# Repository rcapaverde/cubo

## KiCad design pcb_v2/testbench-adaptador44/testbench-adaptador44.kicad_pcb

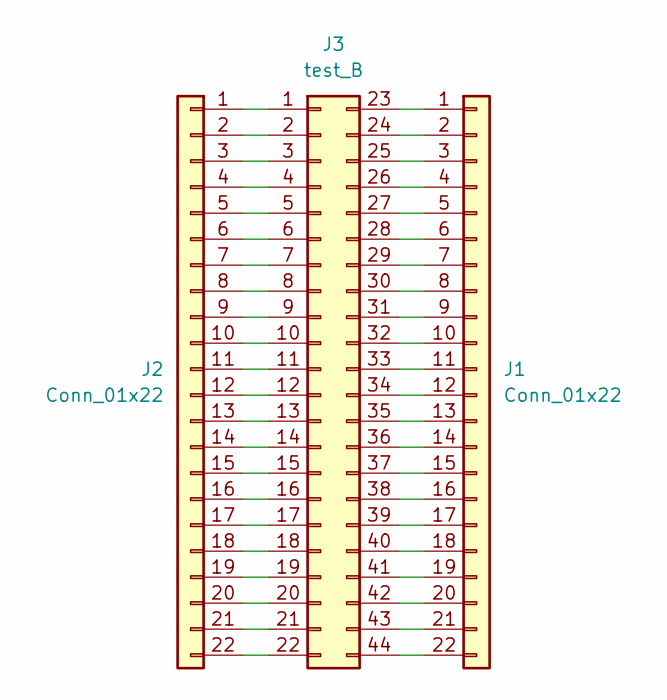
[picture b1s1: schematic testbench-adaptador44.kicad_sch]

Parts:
J1, J2: Conn_01x22; PinHeader_1x22_P2.54mm_Vertical
J3: test_B; male-edge-connector-44

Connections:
unnamed: J1.1, J3.23
unnamed: J1.2, J3.24
unnamed: J1.3, J3.25
unnamed: J1.4, J3.26
unnamed: J1.5, J3.27
unnamed: J1.6, J3.28
unnamed: J1.7, J3.29
unnamed: J1.8, J3.30
unnamed: J1.9, J3.31
unnamed: J1.10, J3.32
unnamed: J1.11, J3.33
unnamed: J1.12, J3.34
unnamed: J1.13, J3.35
unnamed: J1.14, J3.36
unnamed: J1.15, J3.37
unnamed: J1.16, J3.38
unnamed: J1.17, J3.39
unnamed: J1.18, J3.40
unnamed: J1.19, J3.41
unnamed: J1.20, J3.42
unnamed: J1.21, J3.43
unnamed: J1.22, J3.44
unnamed: J2.1, J3.1
unnamed: J2.2, J3.2
unnamed: J2.3, J3.3
unnamed: J2.4, J3.4
unnamed: J2.5, J3.5
unnamed: J2.6, J3.6
unnamed: J2.7, J3.7
unnamed: J2.8, J3.8
unnamed: J2.9, J3.9
unnamed: J2.10, J3.10
unnamed: J2.11, J3.11
unnamed: J2.12, J3.12
unnamed: J2.13, J3.13
unnamed: J2.14, J3.14
unnamed: J2.15, J3.15
unnamed: J2.16, J3.16
unnamed: J2.17, J3.17
unnamed: J2.18, J3.18
unnamed: J2.19, J3.19
unnamed: J2.20, J3.20
unnamed: J2.21, J3.21
unnamed: J2.22, J3.22

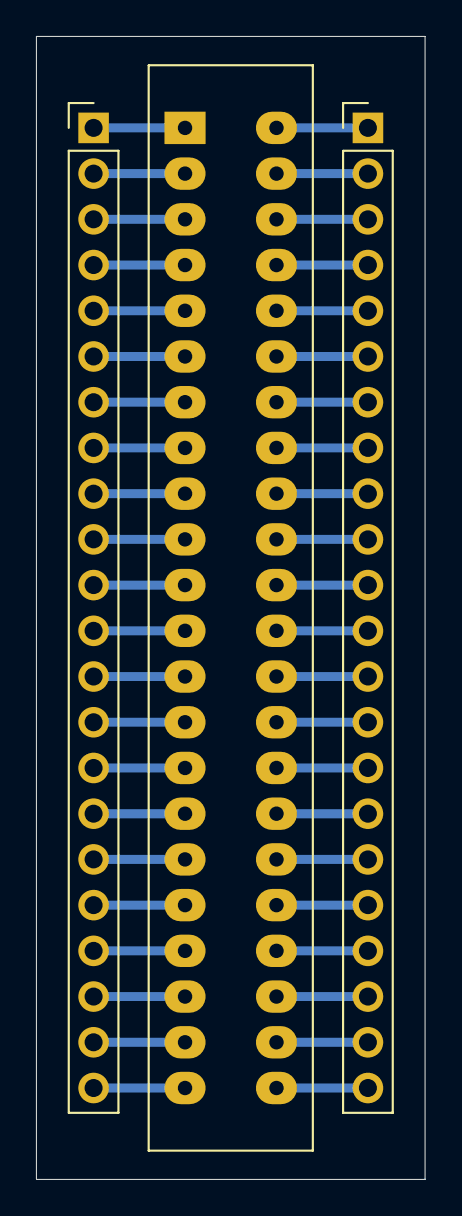
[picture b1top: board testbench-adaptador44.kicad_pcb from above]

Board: 2 copper layers, 21.6 x 63.5 mm, 3 parts (0 on the bottom side), 44 nets.

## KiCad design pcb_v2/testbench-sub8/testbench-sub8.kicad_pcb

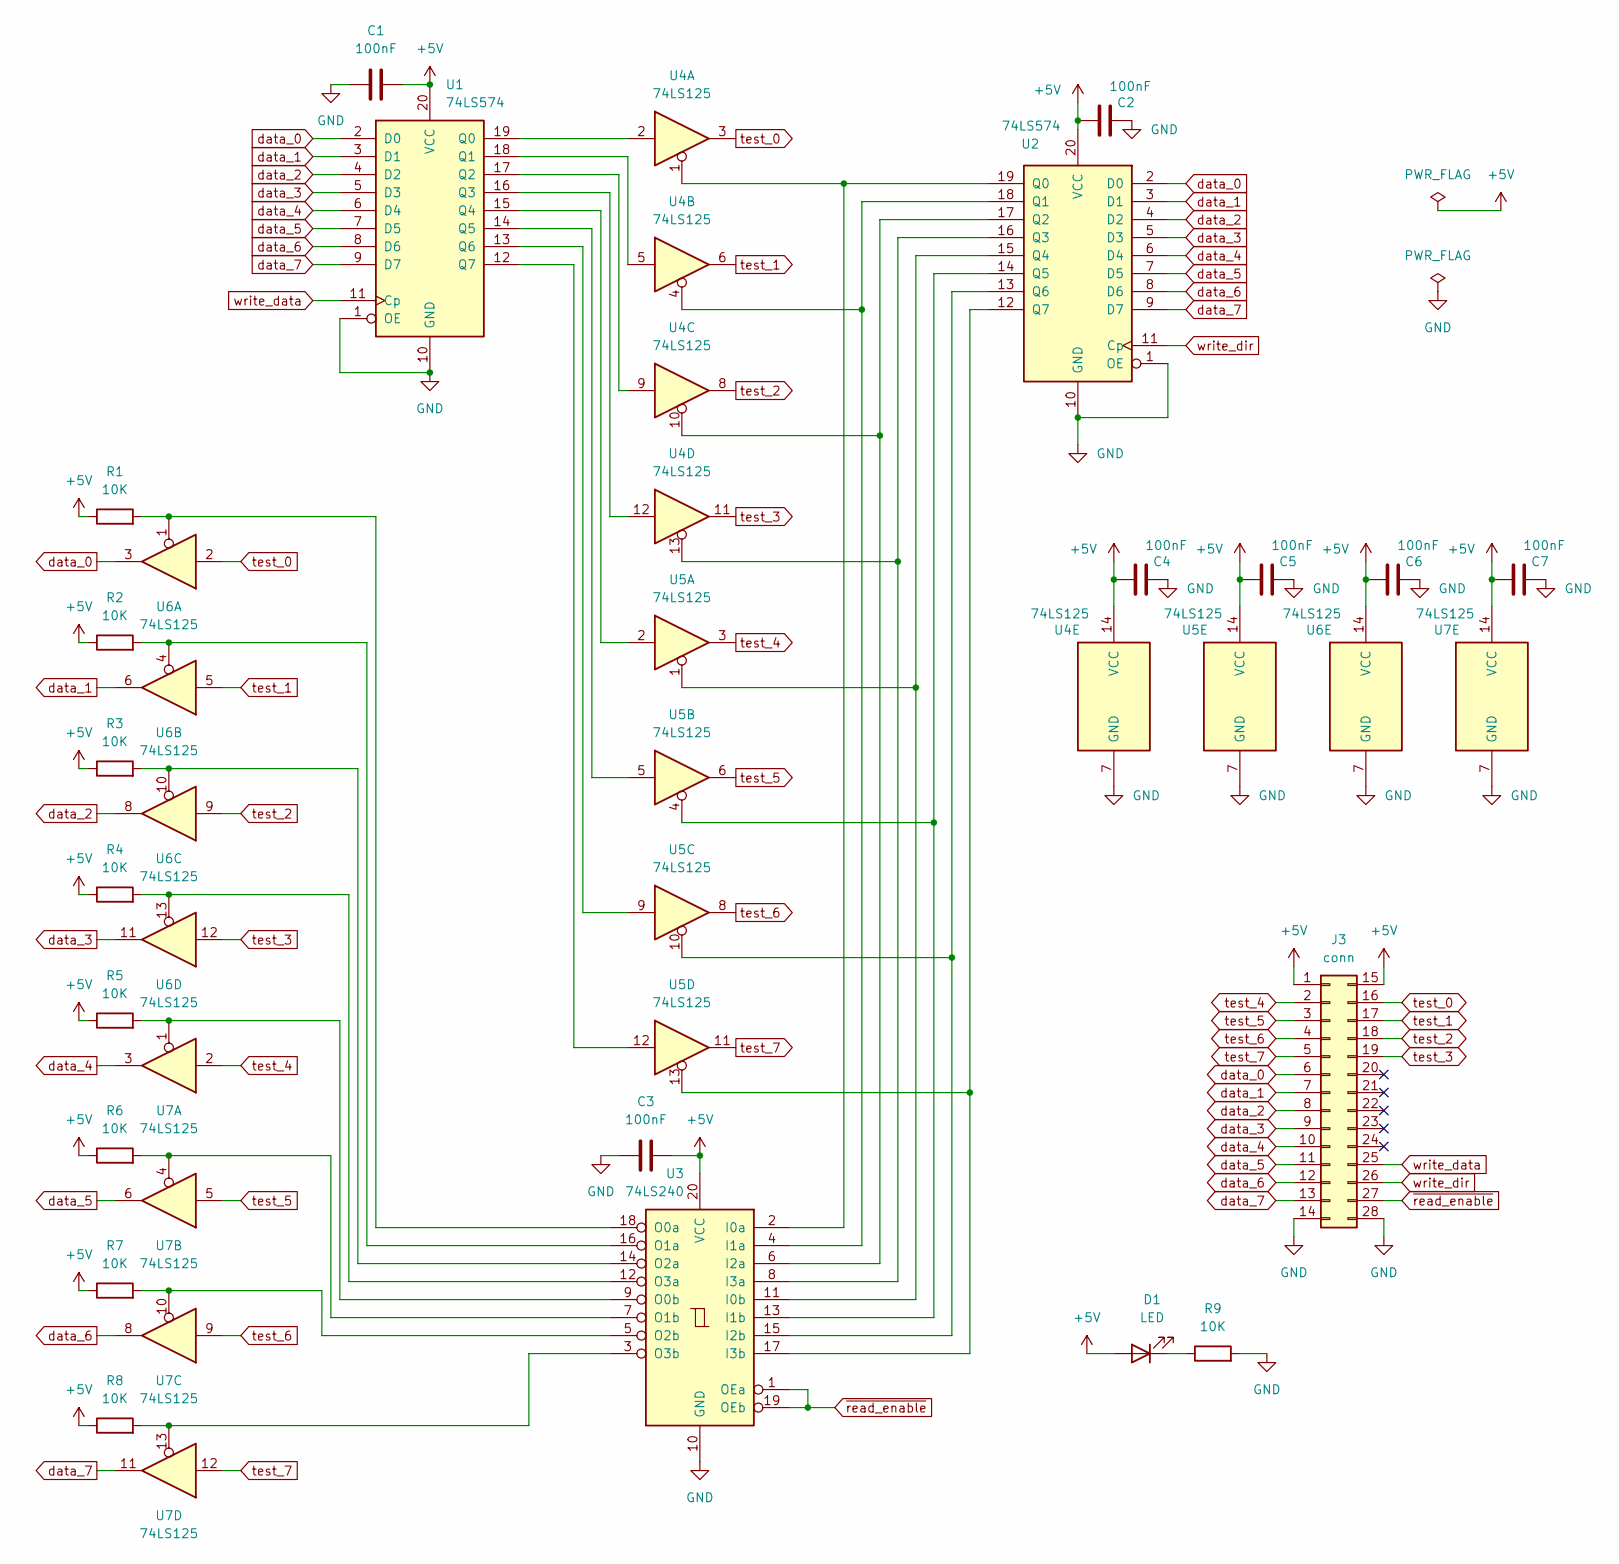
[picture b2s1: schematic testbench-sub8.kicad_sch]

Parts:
C1, C2, C3, C4, C5, C6, C7: 100nF; C_Disc_D4.7mm_W2.5mm_P5.00mm
D1: LED; LED_D5.0mm
J3: conn; edge-conector-14
R1, R2, R3, R4, R5, R6, R7, R8, R9: 10K; R_Axial_DIN0204_L3.6mm_D1.6mm_P7.62mm_Horizontal
U1, U2: 74LS574; DIP-20_W7.62mm
U3: 74LS240; DIP-20_W7.62mm
U4, U5, U6, U7: 74LS125; DIP-14_W7.62mm

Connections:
+5V: C1.2, C2.2, C3.2, C4.2, C5.2, C6.2, C7.2, D1.2 (A), J3.1, J3.15, R1.1, R2.1, R3.1, R4.1, R5.1, R6.1, R7.1, R8.1, U1.20 (VCC), U2.20 (VCC), U3.20 (VCC), U4.14 (VCC), U5.14 (VCC), U6.14 (VCC), U7.14 (VCC)
GND: C1.1, C2.1, C3.1, C4.1, C5.1, C6.1, C7.1, J3.14, J3.28, R9.2, U1.1 (OE), U1.10 (GND), U2.1 (OE), U2.10 (GND), U3.10 (GND), U4.7 (GND), U5.7 (GND), U6.7 (GND), U7.7 (GND)
unnamed: D1.1 (K), R9.1
unnamed: U1.19 (Q0), U4.2
unnamed: U1.18 (Q1), U4.5
unnamed: U1.17 (Q2), U4.9
unnamed: U1.16 (Q3), U4.12
unnamed: U1.15 (Q4), U5.2
unnamed: U1.14 (Q5), U5.5
unnamed: U1.13 (Q6), U5.9
unnamed: U1.12 (Q7), U5.12
unnamed: U2.19 (Q0), U3.2 (I0a), U4.1
unnamed: U2.18 (Q1), U3.4 (I1a), U4.4
unnamed: U2.17 (Q2), U3.6 (I2a), U4.10
unnamed: U2.16 (Q3), U3.8 (I3a), U4.13
unnamed: U2.15 (Q4), U3.11 (I0b), U5.1
unnamed: U2.14 (Q5), U3.13 (I1b), U5.4
unnamed: U2.13 (Q6), U3.15 (I2b), U5.10
unnamed: U2.12 (Q7), U3.17 (I3b), U5.13
unnamed: R1.2, U3.18 (O0a), U6.1
unnamed: R5.2, U3.9 (O0b), U7.1
unnamed: R2.2, U3.16 (O1a), U6.4
unnamed: R6.2, U3.7 (O1b), U7.4
unnamed: R3.2, U3.14 (O2a), U6.10
unnamed: R7.2, U3.5 (O2b), U7.10
unnamed: R4.2, U3.12 (O3a), U6.13
unnamed: R8.2, U3.3 (O3b), U7.13
data_0: J3.6, U1.2 (D0), U2.2 (D0), U6.3
data_1: J3.7, U1.3 (D1), U2.3 (D1), U6.6
data_2: J3.8, U1.4 (D2), U2.4 (D2), U6.8
data_3: J3.9, U1.5 (D3), U2.5 (D3), U6.11
data_4: J3.10, U1.6 (D4), U2.6 (D4), U7.3
data_5: J3.11, U1.7 (D5), U2.7 (D5), U7.6
data_6: J3.12, U1.8 (D6), U2.8 (D6), U7.8
data_7: J3.13, U1.9 (D7), U2.9 (D7), U7.11
test_0: J3.16, U4.3, U6.2
test_1: J3.17, U4.6, U6.5
test_2: J3.18, U4.8, U6.9
test_3: J3.19, U4.11, U6.12
test_4: J3.2, U5.3, U7.2
test_5: J3.3, U5.6, U7.5
test_6: J3.4, U5.8, U7.9
test_7: J3.5, U5.11, U7.12
write_data: J3.25, U1.11 (Cp)
write_dir: J3.26, U2.11 (Cp)
~read_enable: J3.27, U3.1 (OEa), U3.19 (OEb)

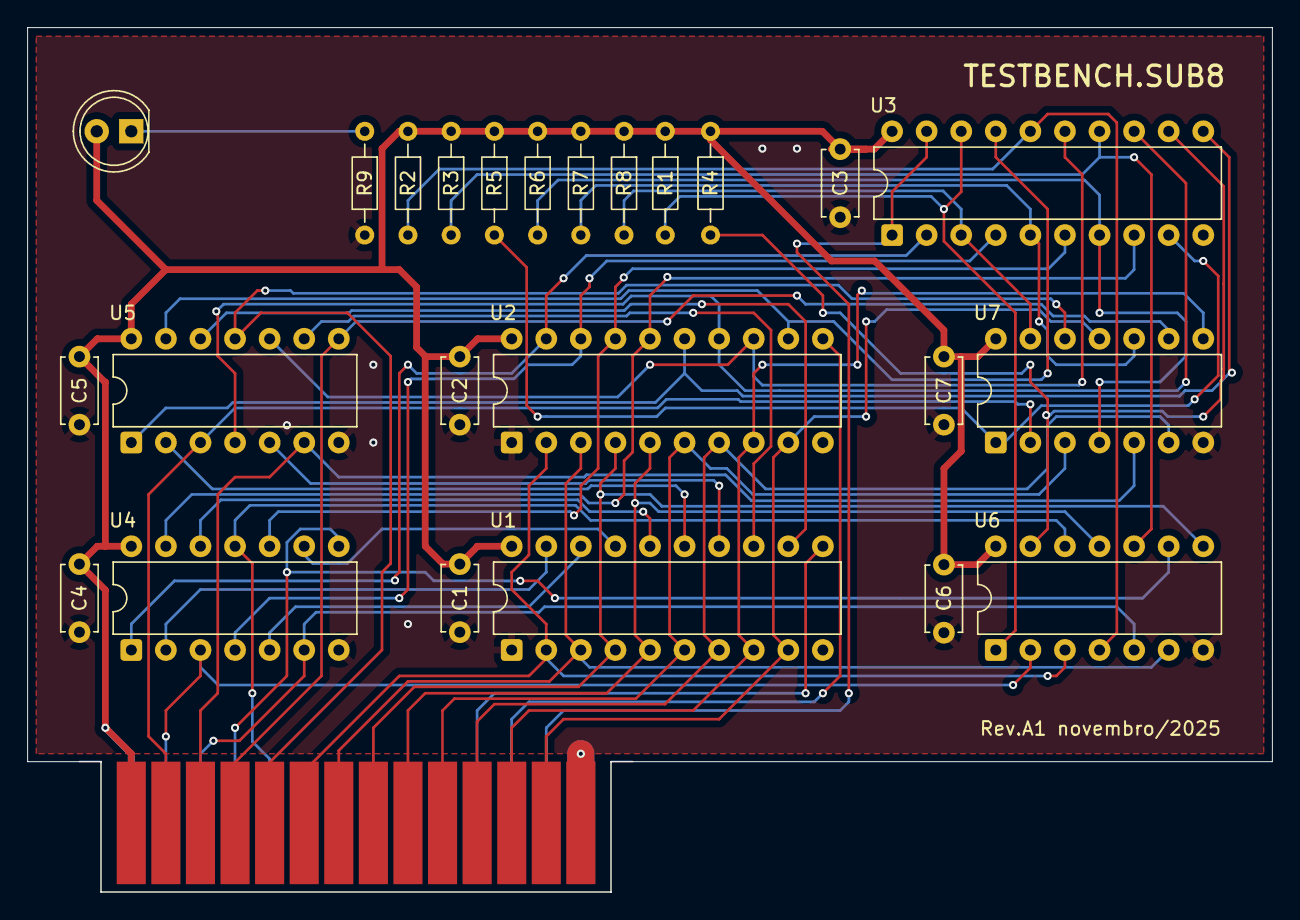
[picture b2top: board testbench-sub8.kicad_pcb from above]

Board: 2 copper layers, 91.4 x 63.5 mm, 25 parts (0 on the bottom side), 46 nets.

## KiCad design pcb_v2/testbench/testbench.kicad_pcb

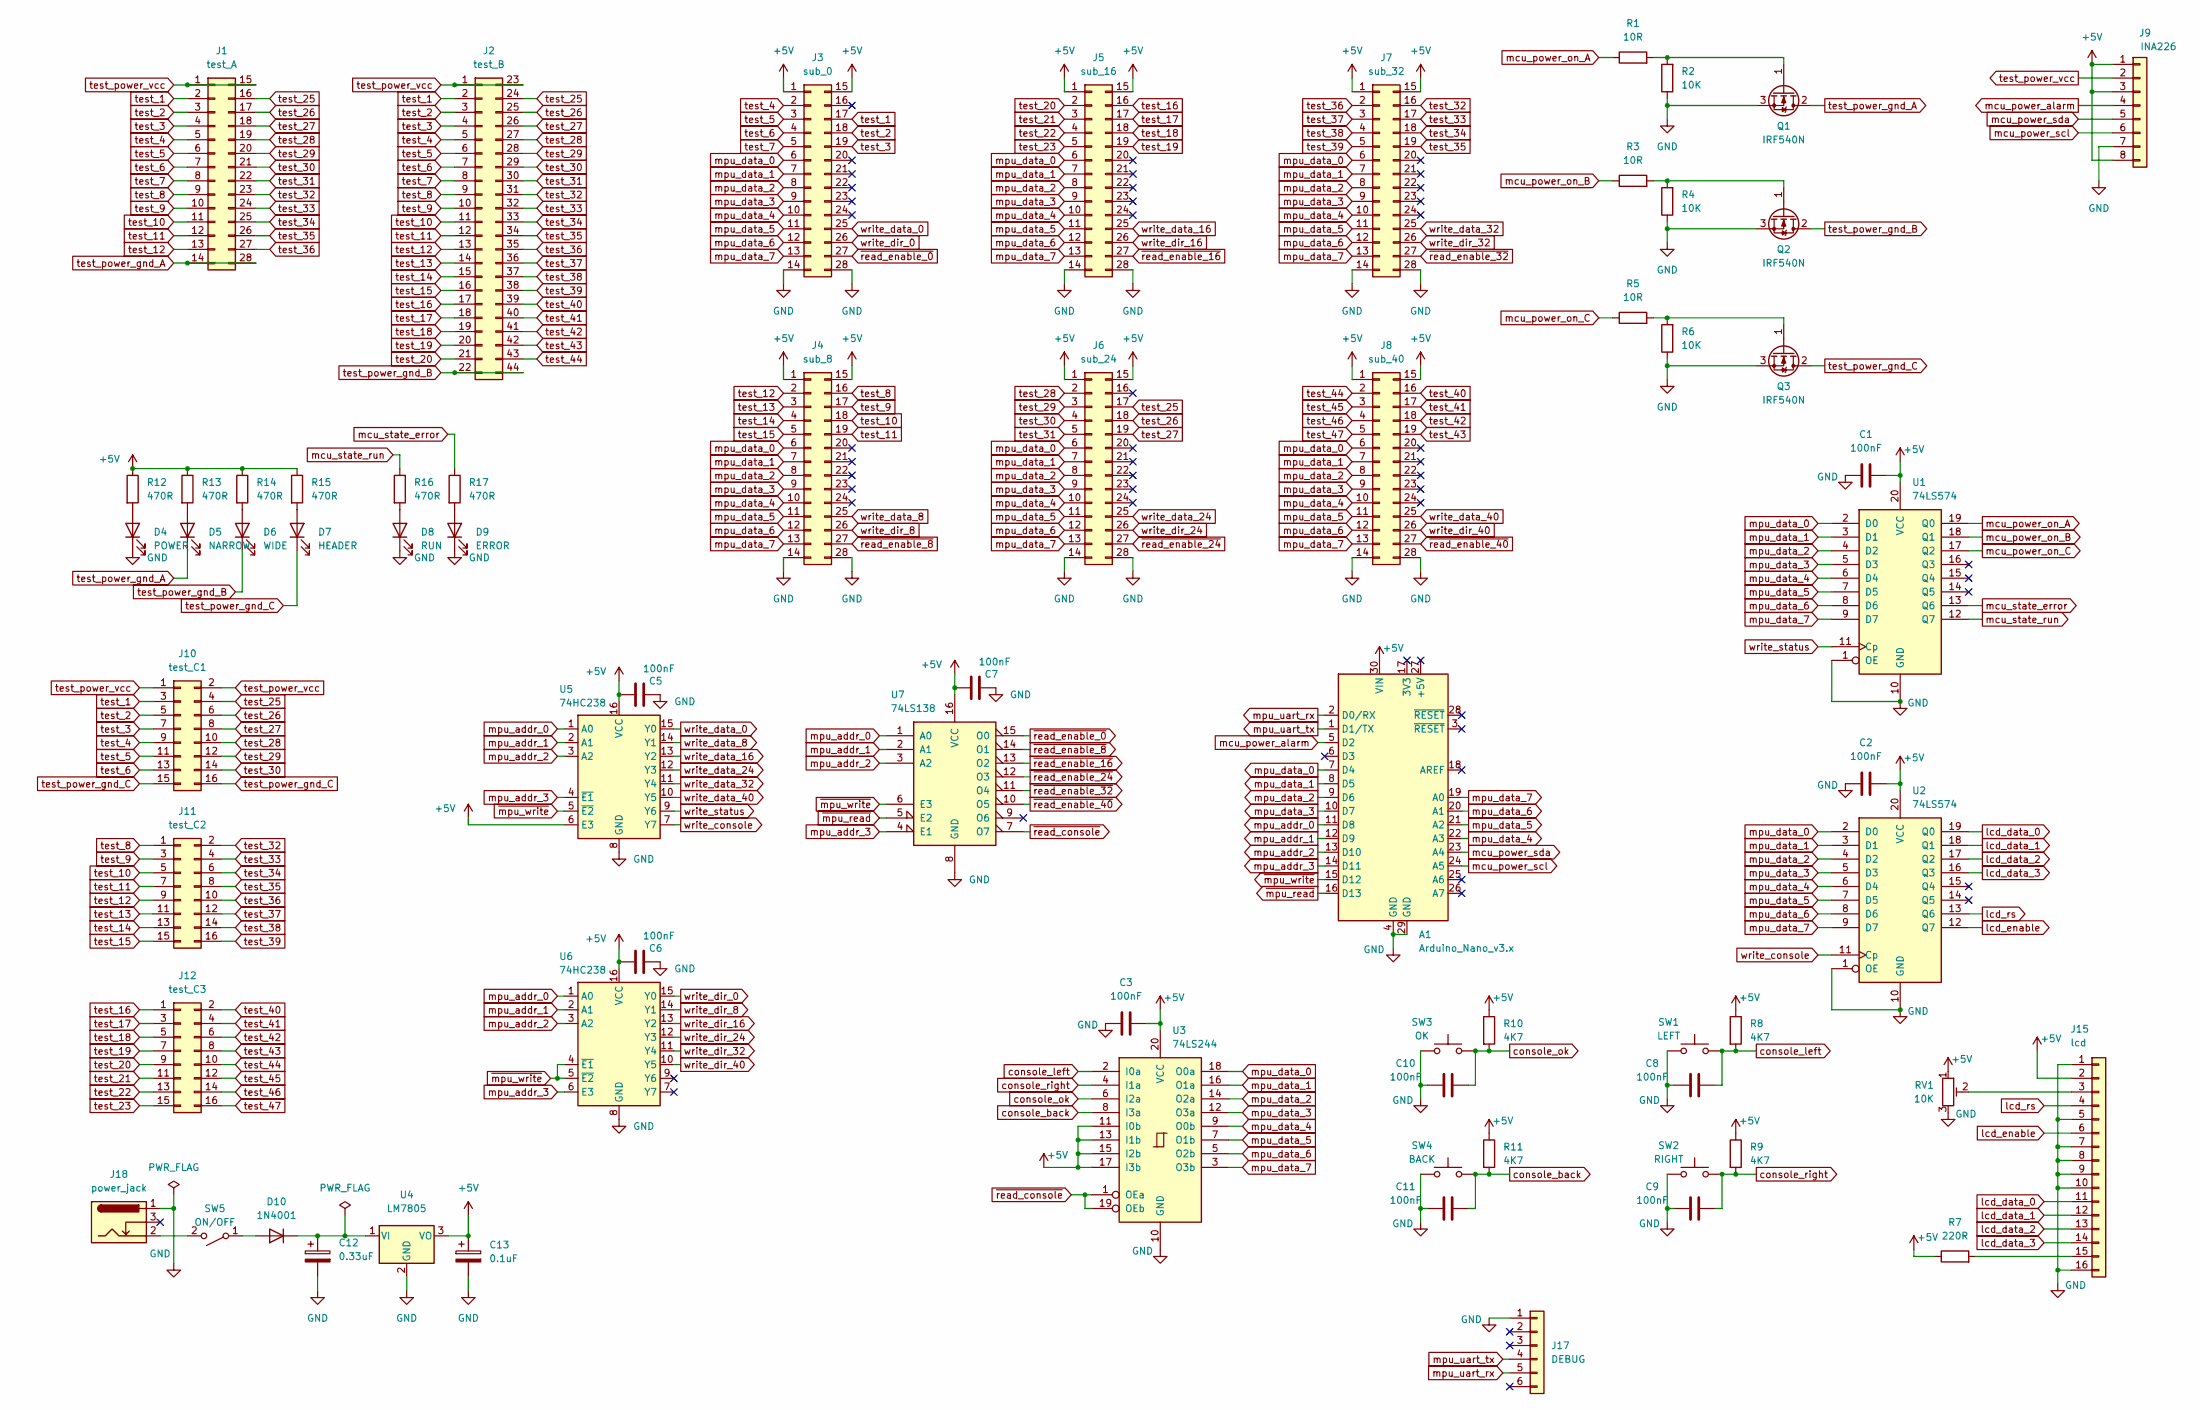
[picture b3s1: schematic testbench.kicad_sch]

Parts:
A1: Arduino_Nano_v3.x; Arduino_Nano
C1, C2, C3, C5, C6, C7, C8, C9, C10, C11: 100nF; C_Disc_D4.7mm_W2.5mm_P5.00mm
C12: 0.33uF; CP_Radial_D5.0mm_P2.50mm
C13: 0.1uF; CP_Radial_D5.0mm_P2.50mm
D4: POWER; LED_D5.0mm
D5: NARROW; LED_D5.0mm
D6: WIDE; LED_D5.0mm
D7: HEADER; LED_D5.0mm
D8: RUN; LED_D5.0mm
D9: ERROR; LED_D5.0mm
D10: 1N4001; D_DO-41_SOD81_P10.16mm_Horizontal
J1: test_A; male-edge-connector-28
J2: test_B; male-edge-connector-44
J3: sub_0; male-edge-connector-28
J4: sub_8; male-edge-connector-28
J5: sub_16; male-edge-connector-28
J6: sub_24; male-edge-connector-28
J7: sub_32; male-edge-connector-28
J8: sub_40; male-edge-connector-28
J9: INA226; PinSocket_1x08_P2.54mm_Vertical
J10: test_C1; PinHeader_2x08_P2.54mm_Vertical
J11: test_C2; PinHeader_2x08_P2.54mm_Vertical
J12: test_C3; PinHeader_2x08_P2.54mm_Vertical
J15: lcd; PinSocket_1x16_P2.54mm_Vertical
J17: DEBUG; PinSocket_1x06_P2.54mm_Vertical
J18: power_jack; BarrelJack_Horizontal
Q1, Q2, Q3: IRF540N; TO-220-3_Vertical
R1, R3, R5: 10R; R_Axial_DIN0207_L6.3mm_D2.5mm_P7.62mm_Horizontal
R2, R4, R6: 10K; R_Axial_DIN0207_L6.3mm_D2.5mm_P7.62mm_Horizontal
R7: 220R; R_Axial_DIN0207_L6.3mm_D2.5mm_P7.62mm_Horizontal
R8, R9, R10, R11: 4K7; R_Axial_DIN0207_L6.3mm_D2.5mm_P7.62mm_Horizontal
R12, R13, R14, R15, R16, R17: 470R; R_Axial_DIN0207_L6.3mm_D2.5mm_P7.62mm_Horizontal
RV1: 10K; Potentiometer_ACP_CA9-H5_Horizontal
SW1: LEFT; SW_PUSH_6mm
SW2: RIGHT; SW_PUSH_6mm
SW3: OK; SW_PUSH_6mm
SW4: BACK; SW_PUSH_6mm
SW5: ON/OFF; jrx
U1, U2: 74LS574; DIP-20_W7.62mm
U3: 74LS244; DIP-20_W7.62mm
U4: LM7805; TO-220-3_Vertical
U5, U6: 74HC238; DIP-16_W7.62mm
U7: 74LS138; DIP-16_W7.62mm

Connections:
+5V: A1.30 (VIN), C1.2, C2.2, C3.2, C5.2, C6.2, C7.2, C13.1, J3.1, J3.15, J4.1, J4.15, J5.1, J5.15, J6.1, J6.15, J7.1, J7.15, J8.1, J8.15, J9.1, J9.3, J9.8, J15.2, R7.1, R8.1, R9.1, R10.1, R11.1, R12.1, R13.1, R14.1, R15.1, RV1.1, U1.20 (VCC), U2.20 (VCC), U3.11 (I0b), U3.13 (I1b), U3.15 (I2b), U3.17 (I3b), U3.20 (VCC), U4.3 (VO), U5.6 (E3), U5.16 (VCC), U6.16 (VCC), U7.16 (VCC)
GND: A1.4 (GND), A1.29 (GND), C1.1, C2.1, C3.1, C5.1, C6.1, C7.1, C8.1, C9.1, C10.1, C11.1, C12.2, C13.2, D4.1 (K), D8.1 (K), D9.1 (K), J3.14, J3.28, J4.14, J4.28, J5.14, J5.28, J6.14, J6.28, J7.14, J7.28, J8.14, J8.28, J9.7, J15.1, J15.5, J15.7, J15.8, J15.9, J15.10, J15.16, J17.1, J18.1, Q1.3 (S), Q2.3 (S), Q3.3 (S), R2.1, R4.1, R6.1, RV1.3, SW1.1, SW2.1, SW3.1, SW4.1, U1.1 (OE), U1.10 (GND), U2.1 (OE), U2.10 (GND), U3.10 (GND), U4.2 (GND), U5.8 (GND), U6.8 (GND), U7.8 (GND)
unnamed: D4.2 (A), R12.2
unnamed: D5.2 (A), R13.2
unnamed: D6.2 (A), R14.2
unnamed: D7.2 (A), R15.2
unnamed: D8.2 (A), R16.2
unnamed: D9.2 (A), R17.2
unnamed: D10.2 (A), SW5.1 (A)
unnamed: C12.1, D10.1 (K), U4.1 (VI)
unnamed: J15.3, RV1.2
unnamed: J15.15, R7.2
unnamed: Q1.1 (G), R1.2, R2.2
unnamed: Q2.1 (G), R3.2, R4.2
unnamed: Q3.1 (G), R5.2, R6.2
unnamed: J18.2, SW5.2 (B)
console_back: C11.2, R11.2, SW4.2, U3.8 (I3a)
console_left: C8.2, R8.2, SW1.2, U3.2 (I0a)
console_ok: C10.2, R10.2, SW3.2, U3.6 (I2a)
console_right: C9.2, R9.2, SW2.2, U3.4 (I1a)
lcd_data_0: J15.11, U2.19 (Q0)
lcd_data_1: J15.12, U2.18 (Q1)
lcd_data_2: J15.13, U2.17 (Q2)
lcd_data_3: J15.14, U2.16 (Q3)
lcd_enable: J15.6, U2.12 (Q7)
lcd_rs: J15.4, U2.13 (Q6)
mcu_power_alarm: A1.5 (D2), J9.4
mcu_power_on_A: R1.1, U1.19 (Q0)
mcu_power_on_B: R3.1, U1.18 (Q1)
mcu_power_on_C: R5.1, U1.17 (Q2)
mcu_power_scl: A1.24 (A5), J9.6
mcu_power_sda: A1.23 (A4), J9.5
mcu_state_error: R17.1, U1.13 (Q6)
mcu_state_run: R16.1, U1.12 (Q7)
mpu_addr_0: A1.11 (D8), U5.1 (A0), U6.1 (A0), U7.1 (A0)
mpu_addr_1: A1.12 (D9), U5.2 (A1), U6.2 (A1), U7.2 (A1)
mpu_addr_2: A1.13 (D10), U5.3 (A2), U6.3 (A2), U7.3 (A2)
mpu_addr_3: A1.14 (D11), U5.4 (~E1), U6.6 (E3), U7.4 (E1)
mpu_data_0: A1.7 (D4), J3.6, J4.6, J5.6, J6.6, J7.6, J8.6, U1.2 (D0), U2.2 (D0), U3.18 (O0a)
mpu_data_1: A1.8 (D5), J3.7, J4.7, J5.7, J6.7, J7.7, J8.7, U1.3 (D1), U2.3 (D1), U3.16 (O1a)
mpu_data_2: A1.9 (D6), J3.8, J4.8, J5.8, J6.8, J7.8, J8.8, U1.4 (D2), U2.4 (D2), U3.14 (O2a)
mpu_data_3: A1.10 (D7), J3.9, J4.9, J5.9, J6.9, J7.9, J8.9, U1.5 (D3), U2.5 (D3), U3.12 (O3a)
mpu_data_4: A1.22 (A3), J3.10, J4.10, J5.10, J6.10, J7.10, J8.10, U1.6 (D4), U2.6 (D4), U3.9 (O0b)
mpu_data_5: A1.21 (A2), J3.11, J4.11, J5.11, J6.11, J7.11, J8.11, U1.7 (D5), U2.7 (D5), U3.7 (O1b)
mpu_data_6: A1.20 (A1), J3.12, J4.12, J5.12, J6.12, J7.12, J8.12, U1.8 (D6), U2.8 (D6), U3.5 (O2b)
mpu_data_7: A1.19 (A0), J3.13, J4.13, J5.13, J6.13, J7.13, J8.13, U1.9 (D7), U2.9 (D7), U3.3 (O3b)
mpu_uart_rx: A1.2 (D0/RX), J17.5
mpu_uart_tx: A1.1 (D1/TX), J17.4
test_1: J1.2, J2.2, J3.17, J10.3
test_2: J1.3, J2.3, J3.18, J10.5
test_3: J1.4, J2.4, J3.19, J10.7
test_4: J1.5, J2.5, J3.2, J10.9
test_5: J1.6, J2.6, J3.3, J10.11
test_6: J1.7, J2.7, J3.4, J10.13
test_7: J1.8, J2.8, J3.5
test_8: J1.9, J2.9, J4.16, J11.1
test_9: J1.10, J2.10, J4.17, J11.3
test_10: J1.11, J2.11, J4.18, J11.5
test_11: J1.12, J2.12, J4.19, J11.7
test_12: J1.13, J2.13, J4.2, J11.9
test_13: J2.14, J4.3, J11.11
test_14: J2.15, J4.4, J11.13
test_15: J2.16, J4.5, J11.15
test_16: J2.17, J5.16, J12.1
test_17: J2.18, J5.17, J12.3
test_18: J2.19, J5.18, J12.5
test_19: J2.20, J5.19, J12.7
test_20: J2.21, J5.2, J12.9
test_21: J5.3, J12.11
test_22: J5.4, J12.13
test_23: J5.5, J12.15
test_25: J1.16, J2.24, J6.17, J10.4
test_26: J1.17, J2.25, J6.18, J10.6
test_27: J1.18, J2.26, J6.19, J10.8
test_28: J1.19, J2.27, J6.2, J10.10
test_29: J1.20, J2.28, J6.3, J10.12
test_30: J1.21, J2.29, J6.4, J10.14
test_31: J1.22, J2.30, J6.5
test_32: J1.23, J2.31, J7.16, J11.2
test_33: J1.24, J2.32, J7.17, J11.4
test_34: J1.25, J2.33, J7.18, J11.6
test_35: J1.26, J2.34, J7.19, J11.8
test_36: J1.27, J2.35, J7.2, J11.10
test_37: J2.36, J7.3, J11.12
test_38: J2.37, J7.4, J11.14
test_39: J2.38, J7.5, J11.16
test_40: J2.39, J8.16, J12.2
test_41: J2.40, J8.17, J12.4
test_42: J2.41, J8.18, J12.6
test_43: J2.42, J8.19, J12.8
test_44: J2.43, J8.2, J12.10
test_45: J8.3, J12.12
test_46: J8.4, J12.14
test_47: J8.5, J12.16
test_power_gnd_A: D5.1 (K), J1.14, J1.28, Q1.2 (D)
test_power_gnd_B: D6.1 (K), J2.22, J2.44, Q2.2 (D)
test_power_gnd_C: D7.1 (K), J10.15, J10.16, Q3.2 (D)
test_power_vcc: J1.1, J1.15, J2.1, J2.23, J9.2, J10.1, J10.2
write_console: U2.11 (Cp), U5.7 (Y7)
write_data_0: J3.25, U5.15 (Y0)
write_data_8: J4.25, U5.14 (Y1)
write_data_16: J5.25, U5.13 (Y2)
write_data_24: J6.25, U5.12 (Y3)
write_data_32: J7.25, U5.11 (Y4)
write_data_40: J8.25, U5.10 (Y5)
write_dir_0: J3.26, U6.15 (Y0)
write_dir_8: J4.26, U6.14 (Y1)
write_dir_16: J5.26, U6.13 (Y2)
write_dir_24: J6.26, U6.12 (Y3)
write_dir_32: J7.26, U6.11 (Y4)
write_dir_40: J8.26, U6.10 (Y5)
write_status: U1.11 (Cp), U5.9 (Y6)
~mpu_read: A1.16 (D13), U7.5 (E2)
~mpu_write: A1.15 (D12), U5.5 (~E2), U6.4 (~E1), U6.5 (~E2), U7.6 (E3)
~read_console: U3.1 (OEa), U3.19 (OEb), U7.7 (O7)
~read_enable_0: J3.27, U7.15 (O0)
~read_enable_8: J4.27, U7.14 (O1)
~read_enable_16: J5.27, U7.13 (O2)
~read_enable_24: J6.27, U7.12 (O3)
~read_enable_32: J7.27, U7.11 (O4)
~read_enable_40: J8.27, U7.10 (O5)

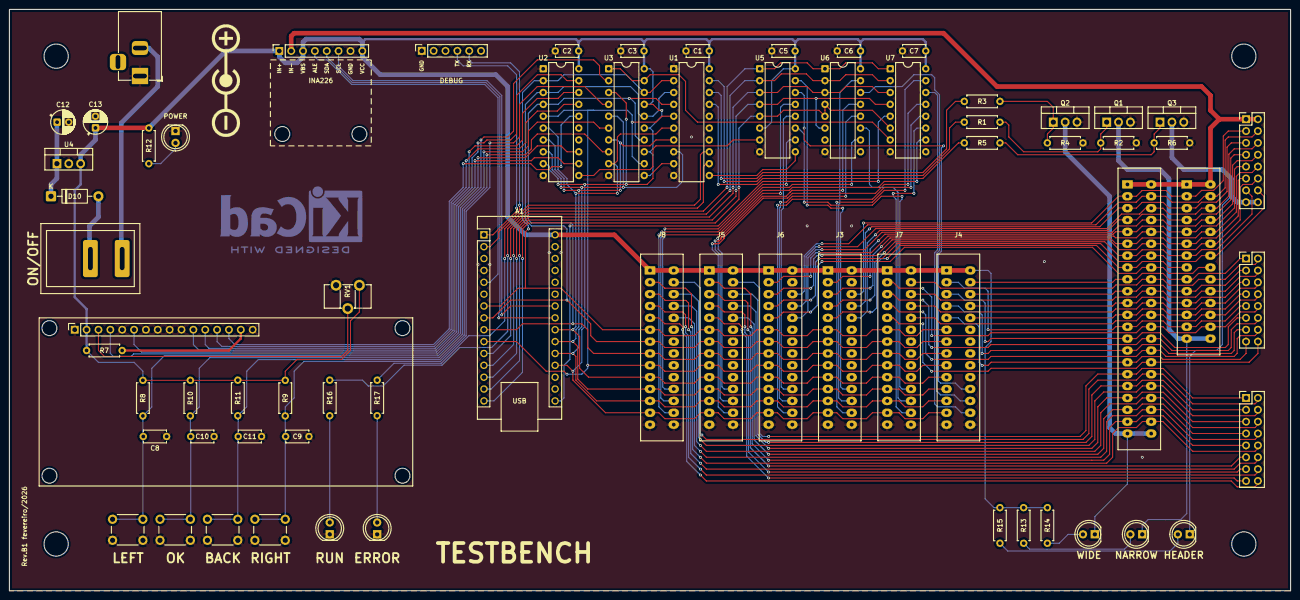
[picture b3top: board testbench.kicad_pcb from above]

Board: 2 copper layers, 274.3 x 124.5 mm, 68 parts (0 on the bottom side), 121 nets.

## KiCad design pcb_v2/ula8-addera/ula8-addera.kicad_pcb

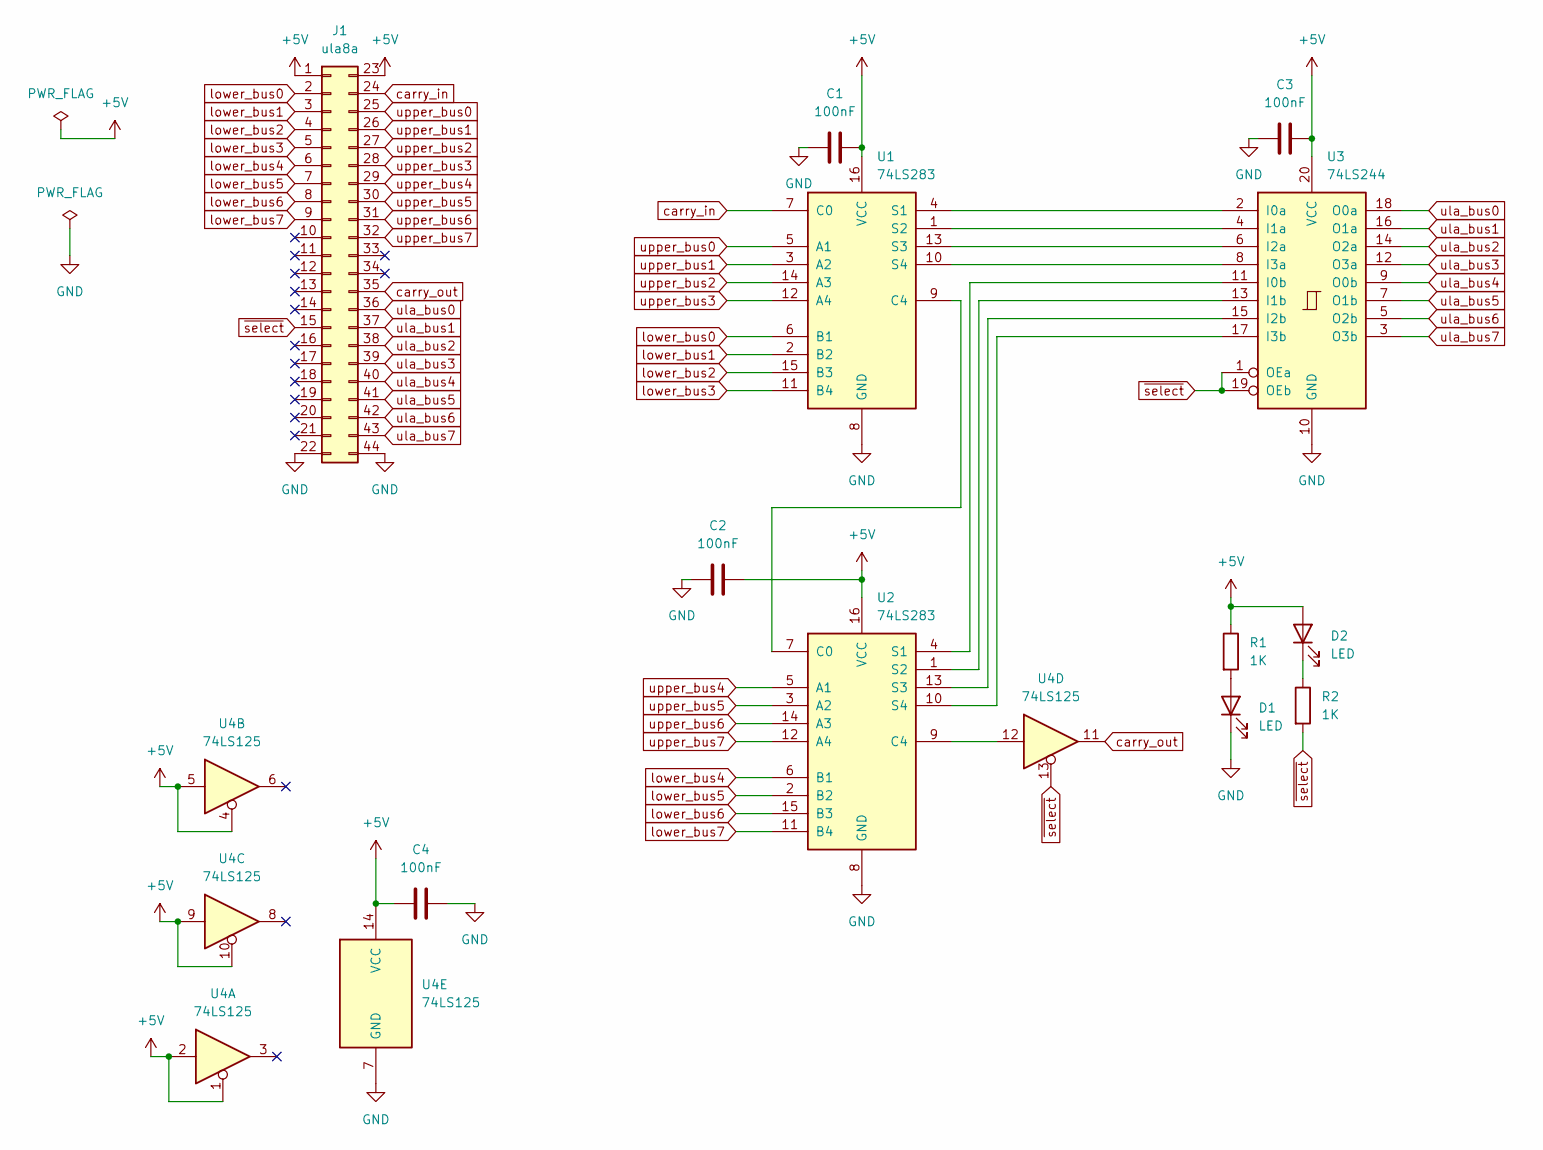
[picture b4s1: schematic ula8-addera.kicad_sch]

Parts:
C1, C2, C3, C4: 100nF; C_Disc_D5.1mm_W3.2mm_P5.00mm
D1, D2: LED; LED_D5.0mm
J1: ula8a; edge-connector-44
R1, R2: 1K; R_Axial_DIN0207_L6.3mm_D2.5mm_P7.62mm_Horizontal
U1, U2: 74LS283; DIP-16_W7.62mm
U3: 74LS244; DIP-20_W7.62mm
U4: 74LS125; DIP-14_W7.62mm

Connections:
+5V: C1.2, C2.2, C3.2, C4.1, D2.2 (A), J1.1, J1.23, R1.1, U1.16 (VCC), U2.16 (VCC), U3.20 (VCC), U4.1, U4.2, U4.4, U4.5, U4.9, U4.10, U4.14 (VCC)
GND: C1.1, C2.1, C3.1, C4.2, D1.1 (K), J1.22, J1.44, U1.8 (GND), U2.8 (GND), U3.10 (GND), U4.7 (GND)
unnamed: D1.2 (A), R1.2
unnamed: D2.1 (K), R2.1
unnamed: U1.9 (C4), U2.7 (C0)
unnamed: U1.4 (S1), U3.2 (I0a)
unnamed: U1.1 (S2), U3.4 (I1a)
unnamed: U1.13 (S3), U3.6 (I2a)
unnamed: U1.10 (S4), U3.8 (I3a)
unnamed: U2.9 (C4), U4.12
unnamed: U2.4 (S1), U3.11 (I0b)
unnamed: U2.1 (S2), U3.13 (I1b)
unnamed: U2.13 (S3), U3.15 (I2b)
unnamed: U2.10 (S4), U3.17 (I3b)
carry_in: J1.24, U1.7 (C0)
carry_out: J1.35, U4.11
lower_bus0: J1.2, U1.6 (B1)
lower_bus1: J1.3, U1.2 (B2)
lower_bus2: J1.4, U1.15 (B3)
lower_bus3: J1.5, U1.11 (B4)
lower_bus4: J1.6, U2.6 (B1)
lower_bus5: J1.7, U2.2 (B2)
lower_bus6: J1.8, U2.15 (B3)
lower_bus7: J1.9, U2.11 (B4)
ula_bus0: J1.36, U3.18 (O0a)
ula_bus1: J1.37, U3.16 (O1a)
ula_bus2: J1.38, U3.14 (O2a)
ula_bus3: J1.39, U3.12 (O3a)
ula_bus4: J1.40, U3.9 (O0b)
ula_bus5: J1.41, U3.7 (O1b)
ula_bus6: J1.42, U3.5 (O2b)
ula_bus7: J1.43, U3.3 (O3b)
upper_bus0: J1.25, U1.5 (A1)
upper_bus1: J1.26, U1.3 (A2)
upper_bus2: J1.27, U1.14 (A3)
upper_bus3: J1.28, U1.12 (A4)
upper_bus4: J1.29, U2.5 (A1)
upper_bus5: J1.30, U2.3 (A2)
upper_bus6: J1.31, U2.14 (A3)
upper_bus7: J1.32, U2.12 (A4)
~select: J1.15, R2.2, U3.1 (OEa), U3.19 (OEb), U4.13

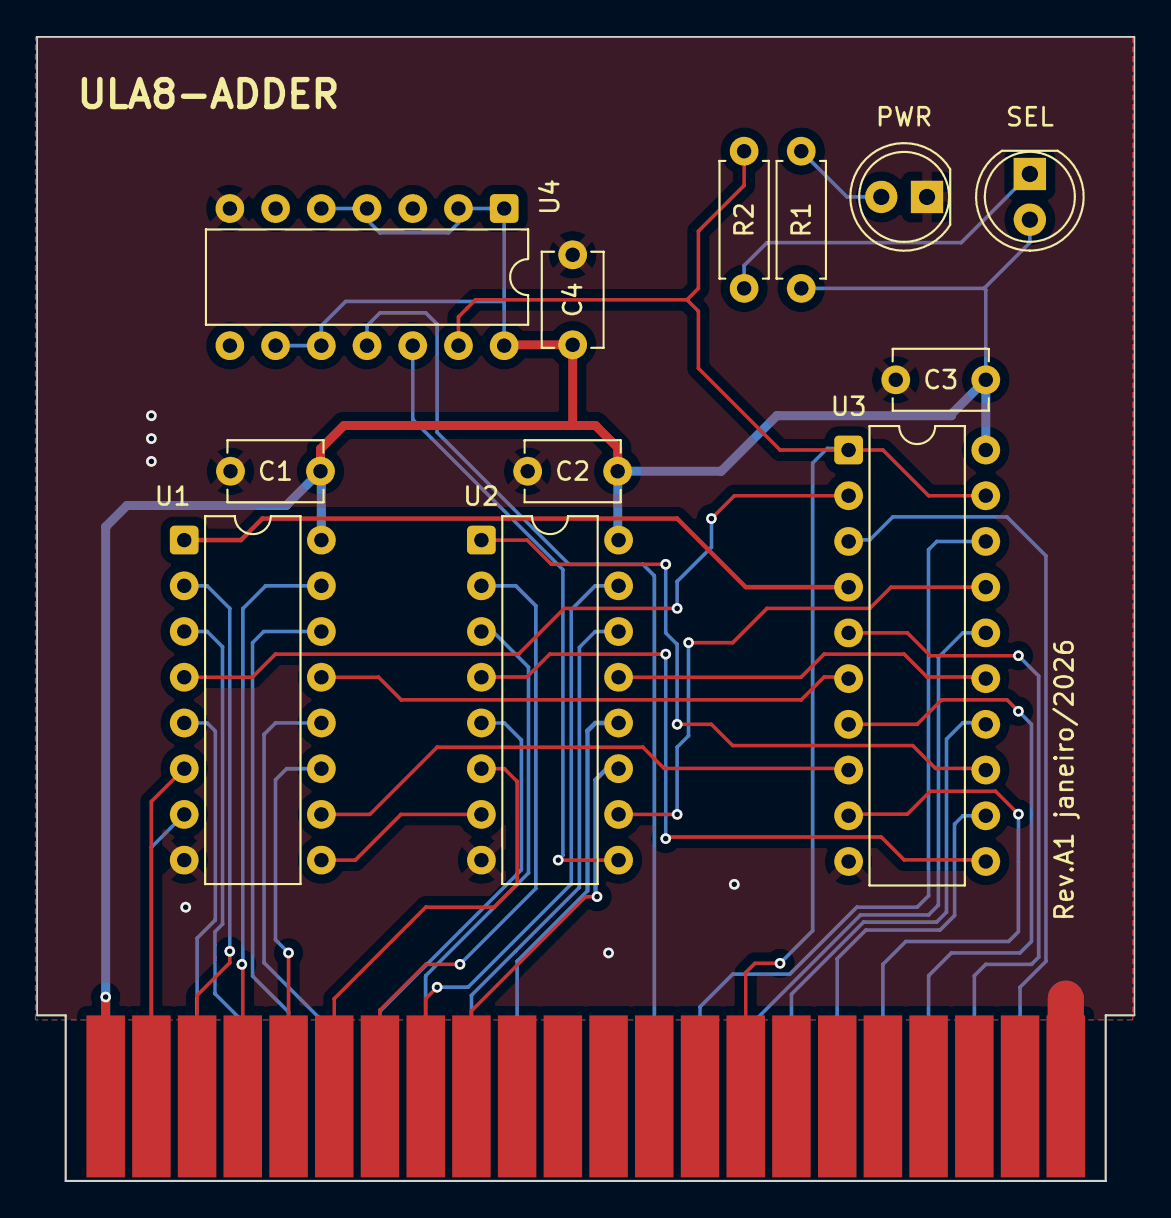
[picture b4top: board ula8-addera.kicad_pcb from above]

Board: 2 copper layers, 61.0 x 63.6 mm, 13 parts (0 on the bottom side), 41 nets.

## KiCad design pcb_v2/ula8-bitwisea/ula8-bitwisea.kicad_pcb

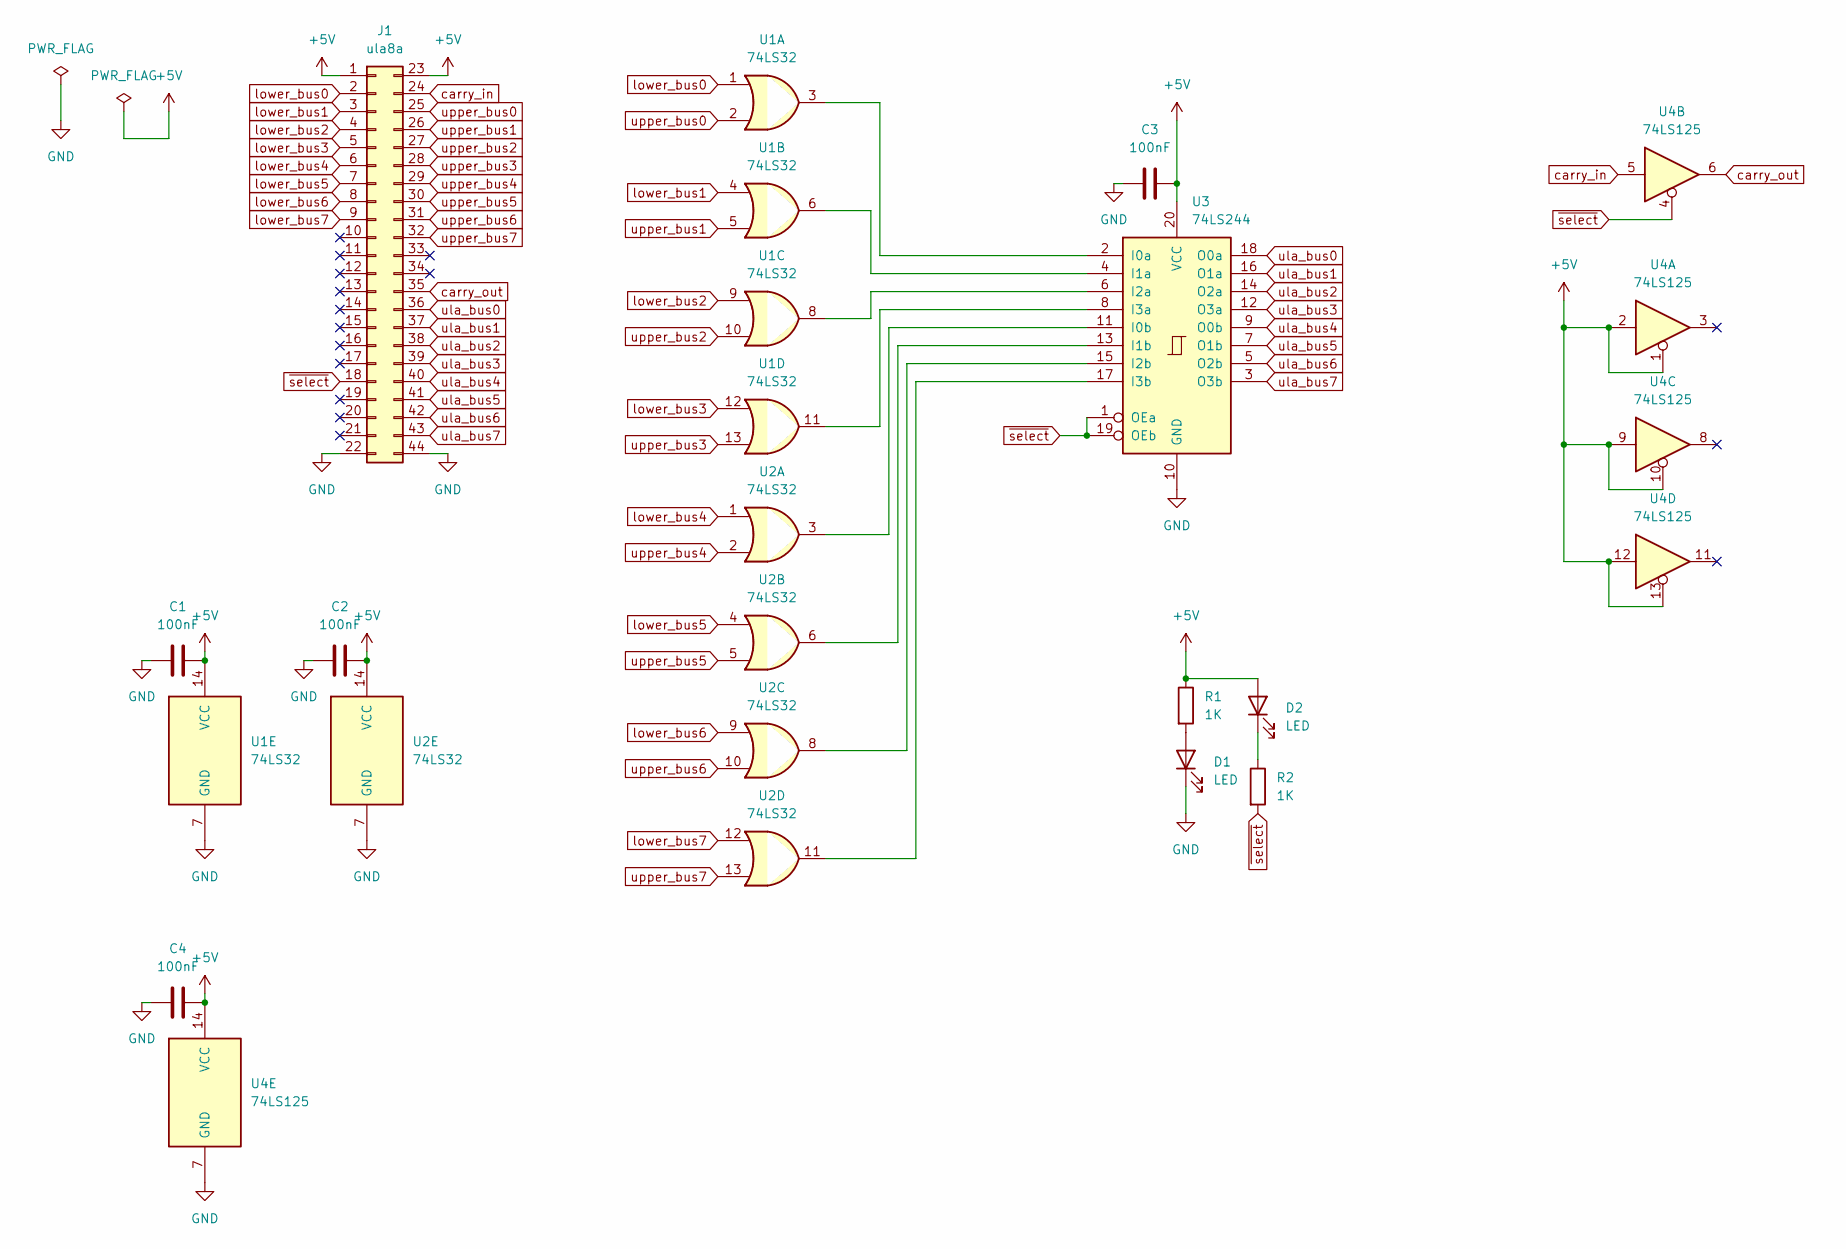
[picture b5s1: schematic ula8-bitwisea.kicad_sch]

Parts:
C1, C2, C3, C4: 100nF; C_Disc_D5.1mm_W3.2mm_P5.00mm
D1, D2: LED; LED_D5.0mm
J1: ula8a; edge-connector-44
R1, R2: 1K; R_Axial_DIN0207_L6.3mm_D2.5mm_P7.62mm_Horizontal
U1, U2: 74LS32; DIP-14_W7.62mm
U3: 74LS244; DIP-20_W7.62mm
U4: 74LS125; DIP-14_W7.62mm

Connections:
+5V: C1.2, C2.2, C3.2, C4.2, D2.2 (A), J1.1, J1.23, R1.1, U1.14 (VCC), U2.14 (VCC), U3.20 (VCC), U4.1, U4.2, U4.9, U4.10, U4.12, U4.13, U4.14 (VCC)
GND: C1.1, C2.1, C3.1, C4.1, D1.1 (K), J1.22, J1.44, U1.7 (GND), U2.7 (GND), U3.10 (GND), U4.7 (GND)
unnamed: D1.2 (A), R1.2
unnamed: D2.1 (K), R2.1
unnamed: U1.3, U3.2 (I0a)
unnamed: U2.3, U3.11 (I0b)
unnamed: U1.6, U3.4 (I1a)
unnamed: U2.6, U3.13 (I1b)
unnamed: U1.8, U3.6 (I2a)
unnamed: U2.8, U3.15 (I2b)
unnamed: U1.11, U3.8 (I3a)
unnamed: U2.11, U3.17 (I3b)
carry_in: J1.24, U4.5
carry_out: J1.35, U4.6
lower_bus0: J1.2, U1.1
lower_bus1: J1.3, U1.4
lower_bus2: J1.4, U1.9
lower_bus3: J1.5, U1.12
lower_bus4: J1.6, U2.1
lower_bus5: J1.7, U2.4
lower_bus6: J1.8, U2.9
lower_bus7: J1.9, U2.12
ula_bus0: J1.36, U3.18 (O0a)
ula_bus1: J1.37, U3.16 (O1a)
ula_bus2: J1.38, U3.14 (O2a)
ula_bus3: J1.39, U3.12 (O3a)
ula_bus4: J1.40, U3.9 (O0b)
ula_bus5: J1.41, U3.7 (O1b)
ula_bus6: J1.42, U3.5 (O2b)
ula_bus7: J1.43, U3.3 (O3b)
upper_bus0: J1.25, U1.2
upper_bus1: J1.26, U1.5
upper_bus2: J1.27, U1.10
upper_bus3: J1.28, U1.13
upper_bus4: J1.29, U2.2
upper_bus5: J1.30, U2.5
upper_bus6: J1.31, U2.10
upper_bus7: J1.32, U2.13
~select: J1.18, R2.2, U3.1 (OEa), U3.19 (OEb), U4.4
